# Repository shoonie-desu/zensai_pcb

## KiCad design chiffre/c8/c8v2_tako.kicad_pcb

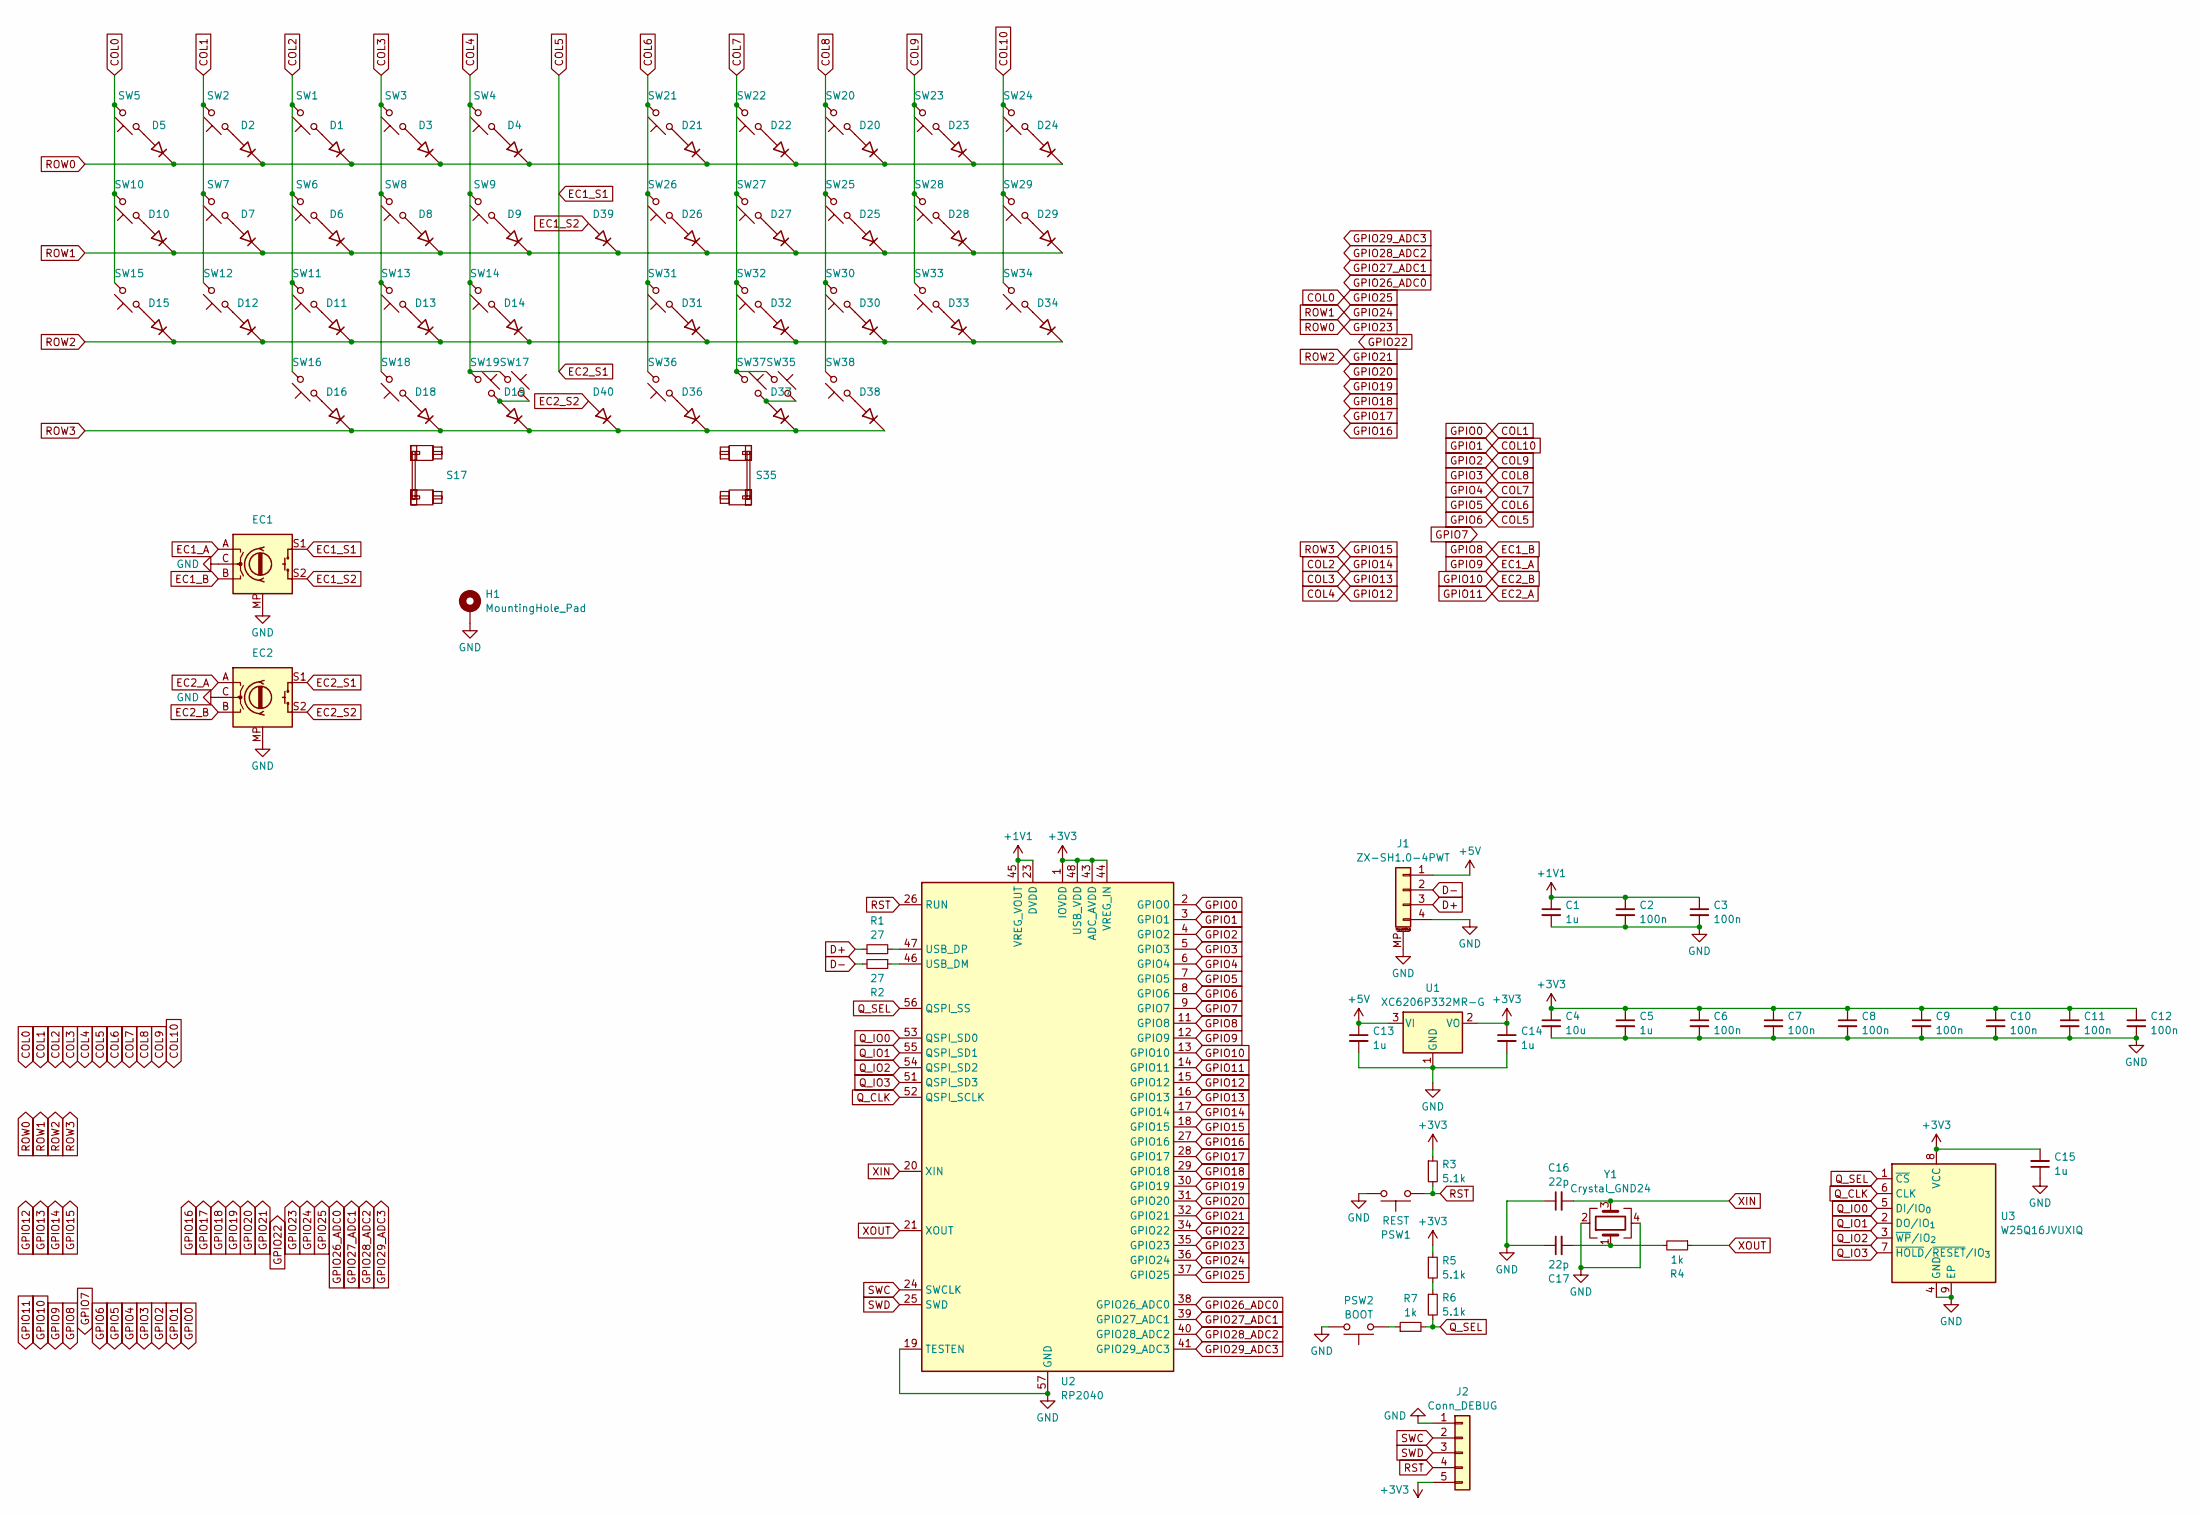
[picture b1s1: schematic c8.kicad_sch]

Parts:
C1, C5, C13, C14, C15: 1u; C_0402_1005Metric_mod
C2, C3, C6, C7, C8, C9, C10, C11, C12: 100n; C_0402_1005Metric_mod
C4: 10u; C_0402_1005Metric_mod
C16, C17: 22p; C_0402_1005Metric_mod
D1, D2, D3, D4, D5, D6, D7, D8, D9, D10, D11, D12, D13, D14, D15, D16, D18, D19, D20, D21, D22, D23, D24, D25, D26, D27, D28, D29, D30, D31, D32, D33, D34, D36, D37, D38, D39, D40: 1N4148W; D_SOD-123_mod
EC1, EC2: RotaryEncoder_Switch_MP; ROT_Alps_EC11E-Switch_mod
H1: MountingHole_Pad; MountingHole_3.2mm_M3_Pad_TopBottom
J1: ZX-SH1.0-4PWT; JST_SH_SM04B-SRSS-TB_1x04-1MP_P1.00mm_Horizontal
J2: Conn_DEBUG; PinHeader_1x05_P1.27mm_Vertical
PSW1: REST; JUMP_REST_10.16mm
PSW2: BOOT; JUMP_BOOT_10.16mm
R1, R2: 27; R_0402_1005Metric
R3, R5, R6: 5.1k; R_0402_1005Metric
R4, R7: 1k; R_0402_1005Metric
S17, S35: MX_S; STAB_MX_2u
SW1, SW2, SW3, SW4, SW5, SW6, SW7, SW8, SW9, SW10, SW11, SW12, SW13, SW14, SW15, SW16, SW17, SW18, SW19, SW20, SW21, SW22, SW23, SW24, SW25, SW26, SW27, SW28, SW29, SW30, SW31, SW32, SW33, SW34, SW35, SW36, SW37, SW38: CPG151101S11; SW_MX_HS_S_CPG151101S11_1u_mod
U1: XC6206P332MR-G; SOT-23-3
U2: RP2040; QFN-56-1EP_7x7mm_P0.4mm_EP3.2x3.2mm
U3: W25Q16JVUXIQ; Winbond_USON-8-1EP_3x2mm_P0.5mm_EP0.2x1.6mm
Y1: Crystal_GND24; Crystal_SMD_3225-4Pin_3.2x2.5mm

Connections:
+1V1: C1.1, C2.1, C3.1, U2.23 (DVDD), U2.45 (VREG_VOUT), U2.50 (DVDD)
+3V3: C4.1, C5.1, C6.1, C7.1, C8.1, C9.1, C10.1, C11.1, C12.1, C14.1, C15.2, J2.5, R3.1, R5.1, U1.2 (VO), U2.1 (IOVDD), U2.10 (IOVDD), U2.22 (IOVDD), U2.33 (IOVDD), U2.42 (IOVDD), U2.43 (ADC_AVDD), U2.44 (VREG_IN), U2.48 (USB_VDD), U2.49 (IOVDD), U3.8 (VCC)
+5V: C13.1, J1.1, U1.3 (VI)
COL0: SW5.2, SW10.2, SW15.2, U2.37 (GPIO25)
COL1: SW2.2, SW7.2, SW12.2, U2.2 (GPIO0)
COL2: SW1.2, SW6.2, SW11.2, SW16.2, U2.17 (GPIO14)
COL3: SW3.2, SW8.2, SW13.2, SW18.2, U2.16 (GPIO13)
COL4: SW4.2, SW9.2, SW14.2, SW17.1, SW19.1, U2.15 (GPIO12)
COL5: EC1.S1, EC2.S1, U2.8 (GPIO6)
COL6: SW21.2, SW26.2, SW31.2, SW36.2, U2.7 (GPIO5)
COL7: SW22.2, SW27.2, SW32.2, SW35.1, SW37.1, U2.6 (GPIO4)
COL8: SW20.2, SW25.2, SW30.2, SW38.2, U2.5 (GPIO3)
COL9: SW23.2, SW28.2, SW33.2, U2.4 (GPIO2)
COL10: SW24.2, SW29.2, SW34.2, U2.3 (GPIO1)
D+: J1.3, R1.1
D-: J1.2, R2.2
EC1_A: EC1.A, U2.12 (GPIO9)
EC1_B: EC1.B, U2.11 (GPIO8)
EC1_S2: D39.2 (A), EC1.S2
EC2_A: EC2.A, U2.14 (GPIO11)
EC2_B: EC2.B, U2.13 (GPIO10)
EC2_S2: D40.2 (A), EC2.S2
GND: C1.2, C2.2, C3.2, C4.2, C5.2, C6.2, C7.2, C8.2, C9.2, C10.2, C11.2, C12.2, C13.2, C14.2, C15.1, C16.1, C17.1, EC1.C, EC1.MP, EC2.C, EC2.MP, H1.1, J1.4, J1.MP (MountPin), J2.1, PSW1.1, PSW2.1, U1.1 (GND), U2.19 (TESTEN), U2.57 (GND), U3.4 (GND), U3.9 (EP), Y1.2, Y1.4; also elsewhere on the board
GPIO7: U2.9 (GPIO7)
GPIO15: D16.1 (K), D18.1 (K), D19.1 (K), D36.1 (K), D37.1 (K), D38.1 (K), D40.1 (K), U2.18 (GPIO15)
GPIO16: U2.27 (GPIO16)
GPIO17: U2.28 (GPIO17)
GPIO18: U2.29 (GPIO18)
GPIO19: U2.30 (GPIO19)
GPIO20: U2.31 (GPIO20)
GPIO21: D11.1 (K), D12.1 (K), D13.1 (K), D14.1 (K), D15.1 (K), D30.1 (K), D31.1 (K), D32.1 (K), D33.1 (K), D34.1 (K), U2.32 (GPIO21)
GPIO22: U2.34 (GPIO22)
GPIO23: D1.1 (K), D2.1 (K), D3.1 (K), D4.1 (K), D5.1 (K), D20.1 (K), D21.1 (K), D22.1 (K), D23.1 (K), D24.1 (K), U2.35 (GPIO23)
GPIO24: D6.1 (K), D7.1 (K), D8.1 (K), D9.1 (K), D10.1 (K), D25.1 (K), D26.1 (K), D27.1 (K), D28.1 (K), D29.1 (K), D39.1 (K), U2.36 (GPIO24)
GPIO26_ADC0: U2.38 (GPIO26_ADC0)
GPIO27_ADC1: U2.39 (GPIO27_ADC1)
GPIO28_ADC2: U2.40 (GPIO28_ADC2)
GPIO29_ADC3: U2.41 (GPIO29_ADC3)
unnamed: C17.2, R4.2, Y1.1
unnamed: D1.2 (A), SW1.1
unnamed: D2.2 (A), SW2.1
unnamed: D3.2 (A), SW3.1
unnamed: D4.2 (A), SW4.1
unnamed: D5.2 (A), SW5.1
unnamed: D6.2 (A), SW6.1
unnamed: D7.2 (A), SW7.1
unnamed: D8.2 (A), SW8.1
unnamed: D9.2 (A), SW9.1
unnamed: D10.2 (A), SW10.1
unnamed: D11.2 (A), SW11.1
unnamed: D12.2 (A), SW12.1
unnamed: D13.2 (A), SW13.1
unnamed: D14.2 (A), SW14.1
unnamed: D15.2 (A), SW15.1
unnamed: D16.2 (A), SW16.1
unnamed: D18.2 (A), SW18.1
unnamed: D19.2 (A), SW17.2, SW19.2
unnamed: D20.2 (A), SW20.1
unnamed: D21.2 (A), SW21.1
unnamed: D22.2 (A), SW22.1
unnamed: D23.2 (A), SW23.1
unnamed: D24.2 (A), SW24.1
unnamed: D25.2 (A), SW25.1
unnamed: D26.2 (A), SW26.1
unnamed: D27.2 (A), SW27.1
unnamed: D28.2 (A), SW28.1
unnamed: D29.2 (A), SW29.1
unnamed: D30.2 (A), SW30.1
unnamed: D31.2 (A), SW31.1
unnamed: D32.2 (A), SW32.1
unnamed: D33.2 (A), SW33.1
unnamed: D34.2 (A), SW34.1
unnamed: D36.2 (A), SW36.1
unnamed: D37.2 (A), SW35.2, SW37.2
unnamed: D38.2 (A), SW38.1
unnamed: PSW2.2, R7.1
unnamed: R5.2, R6.1
unnamed: R2.1, U2.46 (USB_DM)
unnamed: R1.2, U2.47 (USB_DP)
Q_CLK: U2.52 (QSPI_SCLK), U3.6 (CLK)
Q_IO0: U2.53 (QSPI_SD0), U3.5 (DI/IO_{0})
Q_IO1: U2.55 (QSPI_SD1), U3.2 (DO/IO_{1})
Q_IO2: U2.54 (QSPI_SD2), U3.3 (~WP/IO_{2})
Q_IO3: U2.51 (QSPI_SD3), U3.7 (~HOLD/~RESET/IO_{3})
Q_SEL: R6.2, R7.2, U2.56 (QSPI_SS), U3.1 (~CS)
RST: J2.4, PSW1.2, R3.2, U2.26 (RUN)
SWC: J2.2, U2.24 (SWCLK)
SWD: J2.3, U2.25 (SWD)
XIN: C16.2, U2.20 (XIN), Y1.3
XOUT: R4.1, U2.21 (XOUT)

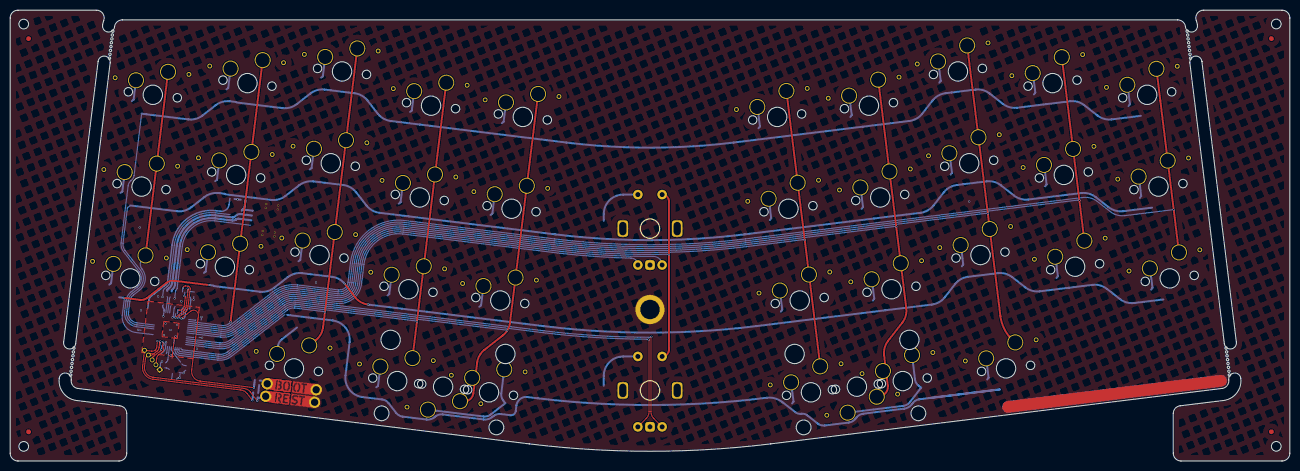
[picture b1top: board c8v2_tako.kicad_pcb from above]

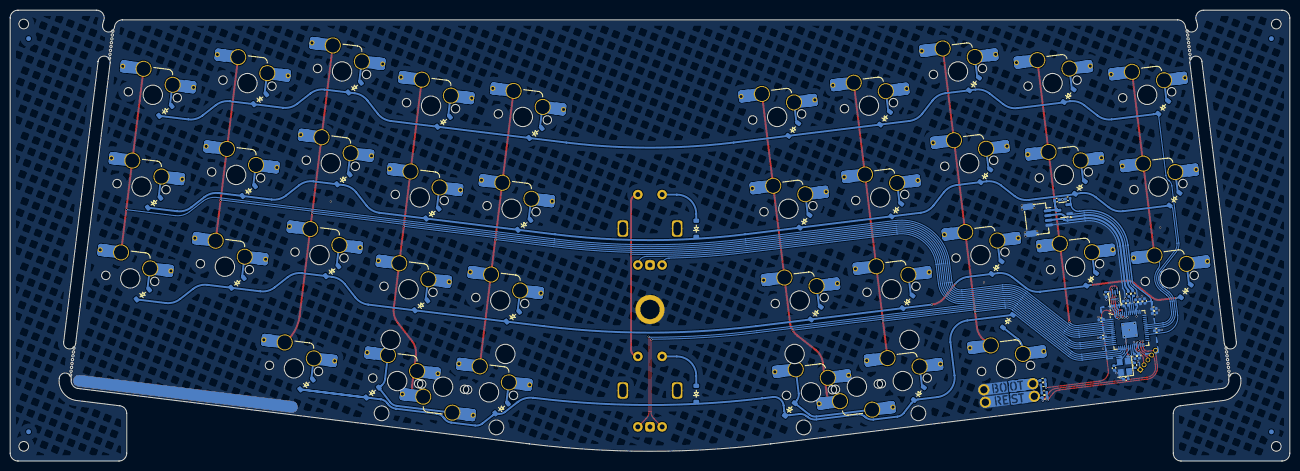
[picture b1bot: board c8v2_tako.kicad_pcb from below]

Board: 2 copper layers, 263.6 x 92.8 mm, 117 parts (111 on the bottom side), 79 nets.

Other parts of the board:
H1#2, H1#3, H1#4, H1#5: MountingHole_Pad; MountingHole_3.2mm_M3_Pad_TopBottom

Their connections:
GND: H1#2.1; also elsewhere on the board

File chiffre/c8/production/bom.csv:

Designator,Footprint,Quantity,Value,LCSC Part #
"C1, C13, C14, C15, C5",0402,5,1u,
"C10, C11, C12, C2, C3, C6, C7, C8, C9",0402,9,100n,
"C16, C17",0402,2,22p,
C4,0402,1,10u,
"D1, D10, D11, D12, D13, D14, D15, D16, D18, D19, D2, D20, D21, D22, D23, D24, D25, D26, D27, D28, D29, D3, D30, D31, D32, D33, D34, D36, D37, D38, D39, D4, D40, D5, D6, D7, D8, D9",D_SOD-123_mod,38,1N4148W,
J1,JST_SH_SM04B-SRSS-TB_1x04-1MP_P1.00mm_Horizontal,1,ZX-SH1.0-4PWT,
"R1, R2",0402,2,27,
"R3, R5, R6",0402,3,5.1k,
"R4, R7",0402,2,1k,
"SW1, SW10, SW11, SW12, SW13, SW14, SW15, SW16, SW17, SW18, SW19, SW2, SW20, SW21, SW22, SW23, SW24, SW25, SW26, SW27, SW28, SW29, SW3, SW30, SW31, SW32, SW33, SW34, SW35, SW36, SW37, SW38, SW4, SW5, SW6, SW7, SW8, SW9",SW_MX_HS_S_CPG151101S11_1u_mod,38,CPG151101S11,
U1,SOT-23-3,1,XC6206P332MR-G,
U2,QFN-56-1EP_7x7mm_P0.4mm_EP3.2x3.2mm,1,RP2040,
U3,Winbond_USON-8-1EP_3x2mm_P0.5mm_EP0.2x1.6mm,1,W25Q16JVUXIQ,
Y1,Crystal_SMD_3225-4Pin_3.2x2.5mm,1,Crystal_GND24,

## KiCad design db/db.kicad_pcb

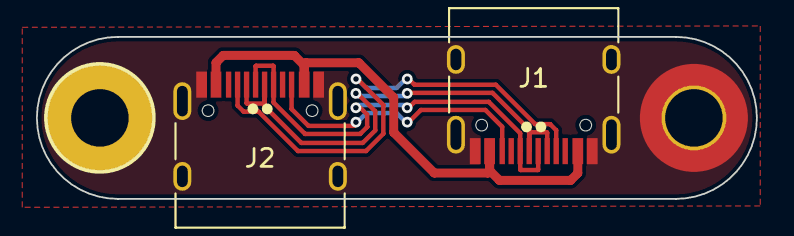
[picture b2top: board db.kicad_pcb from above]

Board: 2 copper layers, 40.0 x 9.0 mm, 4 parts (0 on the bottom side), 6 nets.

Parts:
H1: MountingHole; MountingHole_3.2mm_M3_DIN965_Pad_TopBottom
H2: MountingHole; MountingHole_3.2mm_M3_DIN965_Pad_TopOnly
J1, J2: USB_C_Receptacle_USB2.0; USB_C_Receptacle_HRO_TYPE-C-31-M-12

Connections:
D+: J1.A7 (D-), J1.B7 (D-), J2.A7 (D-), J2.B7 (D-)
D-: J1.A6 (D+), J1.B6 (D+), J2.A6 (D+), J2.B6 (D+)
GND: H1.1, H2.1, J1.A1 (GND), J1.A12 (GND), J1.B1 (GND), J1.B12 (GND), J1.S1 (SHIELD), J2.A1 (GND), J2.A12 (GND), J2.B1 (GND), J2.B12 (GND), J2.S1 (SHIELD)
unnamed: J1.A5 (CC1), J2.A5 (CC1)
unnamed: J1.B5 (CC2), J2.B5 (CC2)
VBUS: J1.A4 (VBUS), J1.A9 (VBUS), J1.B4 (VBUS), J1.B9 (VBUS), J2.A4 (VBUS), J2.A9 (VBUS), J2.B4 (VBUS), J2.B9 (VBUS)

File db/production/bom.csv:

Designator,Footprint,Quantity,Value,LCSC Part #
"J1, J2",USB_C_Receptacle_HRO_TYPE-C-31-M-12,2,USB_C_Receptacle_USB2.0,
